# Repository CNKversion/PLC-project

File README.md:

# PLC-project
a PLC project 
act. > revisar earth del transistor de los relés, revisar capas, optimizar tamaños

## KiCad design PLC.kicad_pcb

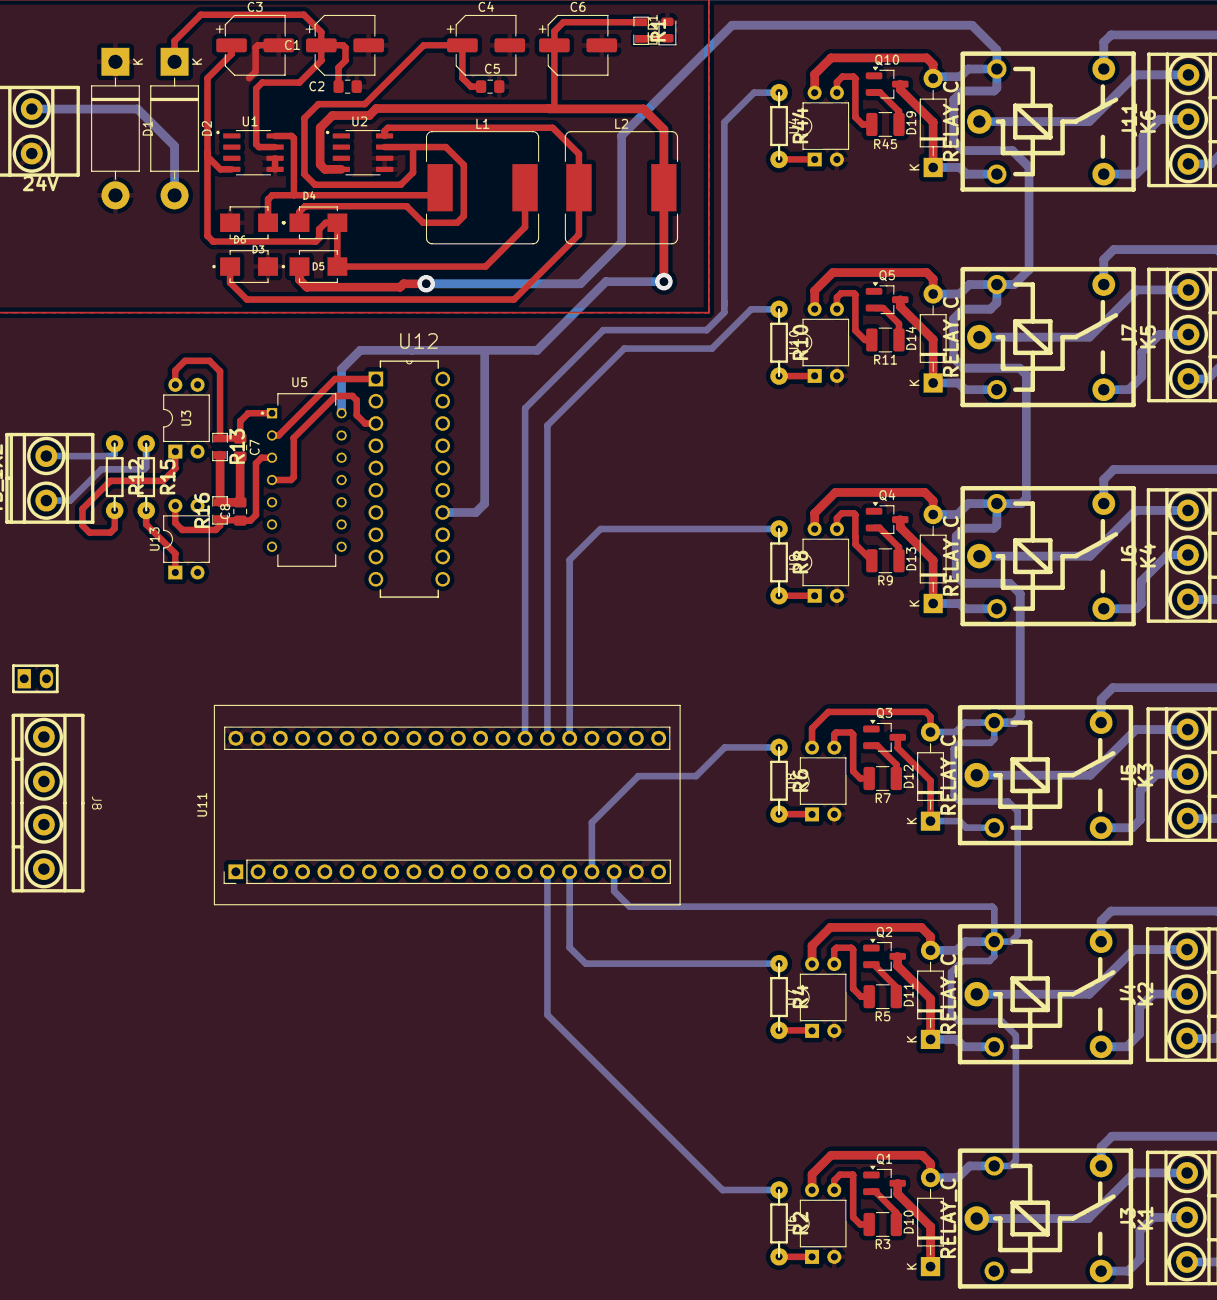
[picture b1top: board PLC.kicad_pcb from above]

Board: 2 copper layers, 75 parts (0 on the bottom side), 72 nets.

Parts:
C1, C4: 470uF; CP_Elec_6.3x7.7
C2, C5: 1uF; C_0805_2012Metric_Pad1.18x1.45mm_HandSolder
C3, C6: 220uF; CP_Elec_6.3x7.7
C7, C8: C; C_0805_2012Metric_Pad1.18x1.45mm_HandSolder
D1, D2: 1N5822; D_DO-201AD_P15.24mm_Horizontal
D3, D4, D5, D6: SS210; DIOM4336X265N
D10, D11, D12, D13, D14, D19: 1N4007; D_DO-41_SOD81_P10.16mm_Horizontal
J1: 24V; BORNERA2
J3, J4, J5, J6, J7, J11: Salida; BORNERA3_AZUL
J8: Screw_Terminal_01x04; Bornera_4
J13: TB_1X2; BORNERA2
JP1: Jumper; Jumper_Alto
K1, K2, K3, K4, K5, K6: RELAY_C; Relay_C
L1, L2: 68uH; L_Bourns_SRR1260
LED1: LED; LED_0805_2012Metric
Q1, Q2, Q3, Q4, Q5, Q10: 2N3904; SOT-23_Handsoldering
R1: 1K; R_0805
R2, R4, R6, R8, R10, R44: 220; RES0.3
R3, R5, R7, R9, R11, R45: 1k; R_1210_3225Metric_Pad1.30x2.65mm_HandSolder
R12, R15: R; RES0.3
R13, R16: R; R_0805
U1: LM2594M-5.0; SOIC127P599X175-8N
U2: LM2594M-3.3; SOIC127P599X175-8N
U3, U4, U6, U7, U8, U9, U10, U13: PC817; DIP-4_W7.62mm
U5: SN74HC14PWR; DIP794W45P254L1969H508Q14
U11: BluePill
U12: SN74HC541PWR; DIP254P762X508-20

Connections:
5V: D5.C, D10.2 (A), D11.2 (A), D12.2 (A), D13.2 (A), D14.2 (A), D19.2 (A), K1.5, K2.5, K3.5, K4.5, K5.5, K6.5, U4.4, U6.4, U7.4, U8.4, U9.4, U10.4, U11.18 (5V)
/1A hc14: C7.1, R13.1, U3.4, U5.1 (1A)
/1Y hc14: U5.2 (1Y), U12.1 (1A)
/2A hc14: C8.1, R16.1, U5.3 (2A), U13.4
/2Y hc14: U5.4 (2Y), U12.3 (2A)
/3Y hc14: U5.6 (3Y), U12.5 (3A)
/4Y hc14: U5.8 (4Y), U12.9 (4A)
/5Y hc14: U5.10 (5Y), U12.11 (5A)
/6Y hc14: U5.12 (6Y), U12.13 (6A)
/IN1: J13.1, R12.1
/IN2: J13.2, R15.1
/PA0: R8.1, U11.25 (PA0)
/PA01: R10.1, U11.26 (PA1)
/PA02: R44.1, U11.27 (PA2)
/PB07: R2.1, U11.15 (PB7)
/PB08: R4.1, U11.16 (PB8)
/PB09: R6.1, U11.17 (PB9)
/VCC: C6.1, C7.2, C8.2, L2.2, R1.1, R13.2, R16.2, U2.4 (FB), U5.14 (VCC), U12.14 (VCC)
Earth: C1.2, C2.2, C3.2, C4.2, C5.2, C6.2, D1.1 (K), D1.2 (A), D3.A, D6.A, J1.2, LED1.2 (K), Q1.1 (E), Q2.1 (E), Q3.1 (E), Q4.1 (E), Q5.1 (E), Q10.1 (E), U1.5 (ON/OFF), U1.6 (GND), U2.5 (ON/OFF), U2.6 (GND), U3.2, U3.3, U5.7 (GND), U12.7 (GND), U13.2, U13.3
GND: U4.2, U6.2, U7.2, U8.2, U9.2, U10.2, U11.19 (GND), U11.39 (GND), U11.40 (GND)
unnamed: C1.1, C2.1, D2.1 (K), U1.7 (VIN)
unnamed: D10.1 (K), K1.2, Q1.3 (C)
unnamed: D11.1 (K), K2.2, Q2.3 (C)
unnamed: D12.1 (K), K3.2, Q3.3 (C)
unnamed: D13.1 (K), K4.2, Q4.3 (C)
unnamed: D14.1 (K), K5.2, Q5.3 (C)
unnamed: D19.1 (K), K6.2, Q10.3 (C)
unnamed: J3.1, K1.4
unnamed: J3.2, K1.3
unnamed: J3.3, K1.1
unnamed: J4.1, K2.4
unnamed: J4.2, K2.3
unnamed: J4.3, K2.1
unnamed: J5.1, K3.4
unnamed: J5.2, K3.3
unnamed: J5.3, K3.1
unnamed: J6.1, K4.4
unnamed: J6.2, K4.3
unnamed: J6.3, K4.1
unnamed: J7.1, K5.4
unnamed: J7.2, K5.3
unnamed: J7.3, K5.1
unnamed: J8.1, JP1.1 (A)
unnamed: J8.2, JP1.2 (B)
unnamed: J11.1, K6.4
unnamed: J11.2, K6.3
unnamed: J11.3, K6.1
unnamed: LED1.1 (A), R1.2
unnamed: Q1.2 (B), R3.1
unnamed: Q2.2 (B), R5.1
unnamed: Q3.2 (B), R7.1
unnamed: Q4.2 (B), R9.1
unnamed: Q5.2 (B), R11.1
unnamed: Q10.2 (B), R45.1
unnamed: R2.2, U6.1
unnamed: R3.2, U6.3
unnamed: R4.2, U7.1
unnamed: R5.2, U7.3
unnamed: R6.2, U8.1
unnamed: R7.2, U8.3
unnamed: R8.2, U9.1
unnamed: R9.2, U9.3
unnamed: R10.2, U10.1
unnamed: R11.2, U10.3
unnamed: R12.2, U3.1
unnamed: R15.2, U13.1
unnamed: R44.2, U4.1
unnamed: R45.2, U4.3
unnamed: C3.1, D4.A, D5.A, L1.2, U1.4 (FB)
unnamed: D3.C, L1.1, U1.8 (OUT)
unnamed: D6.C, L2.1, U2.8 (OUT)
unnamed: C4.1, C5.1, D4.C, U2.7 (VIN)
